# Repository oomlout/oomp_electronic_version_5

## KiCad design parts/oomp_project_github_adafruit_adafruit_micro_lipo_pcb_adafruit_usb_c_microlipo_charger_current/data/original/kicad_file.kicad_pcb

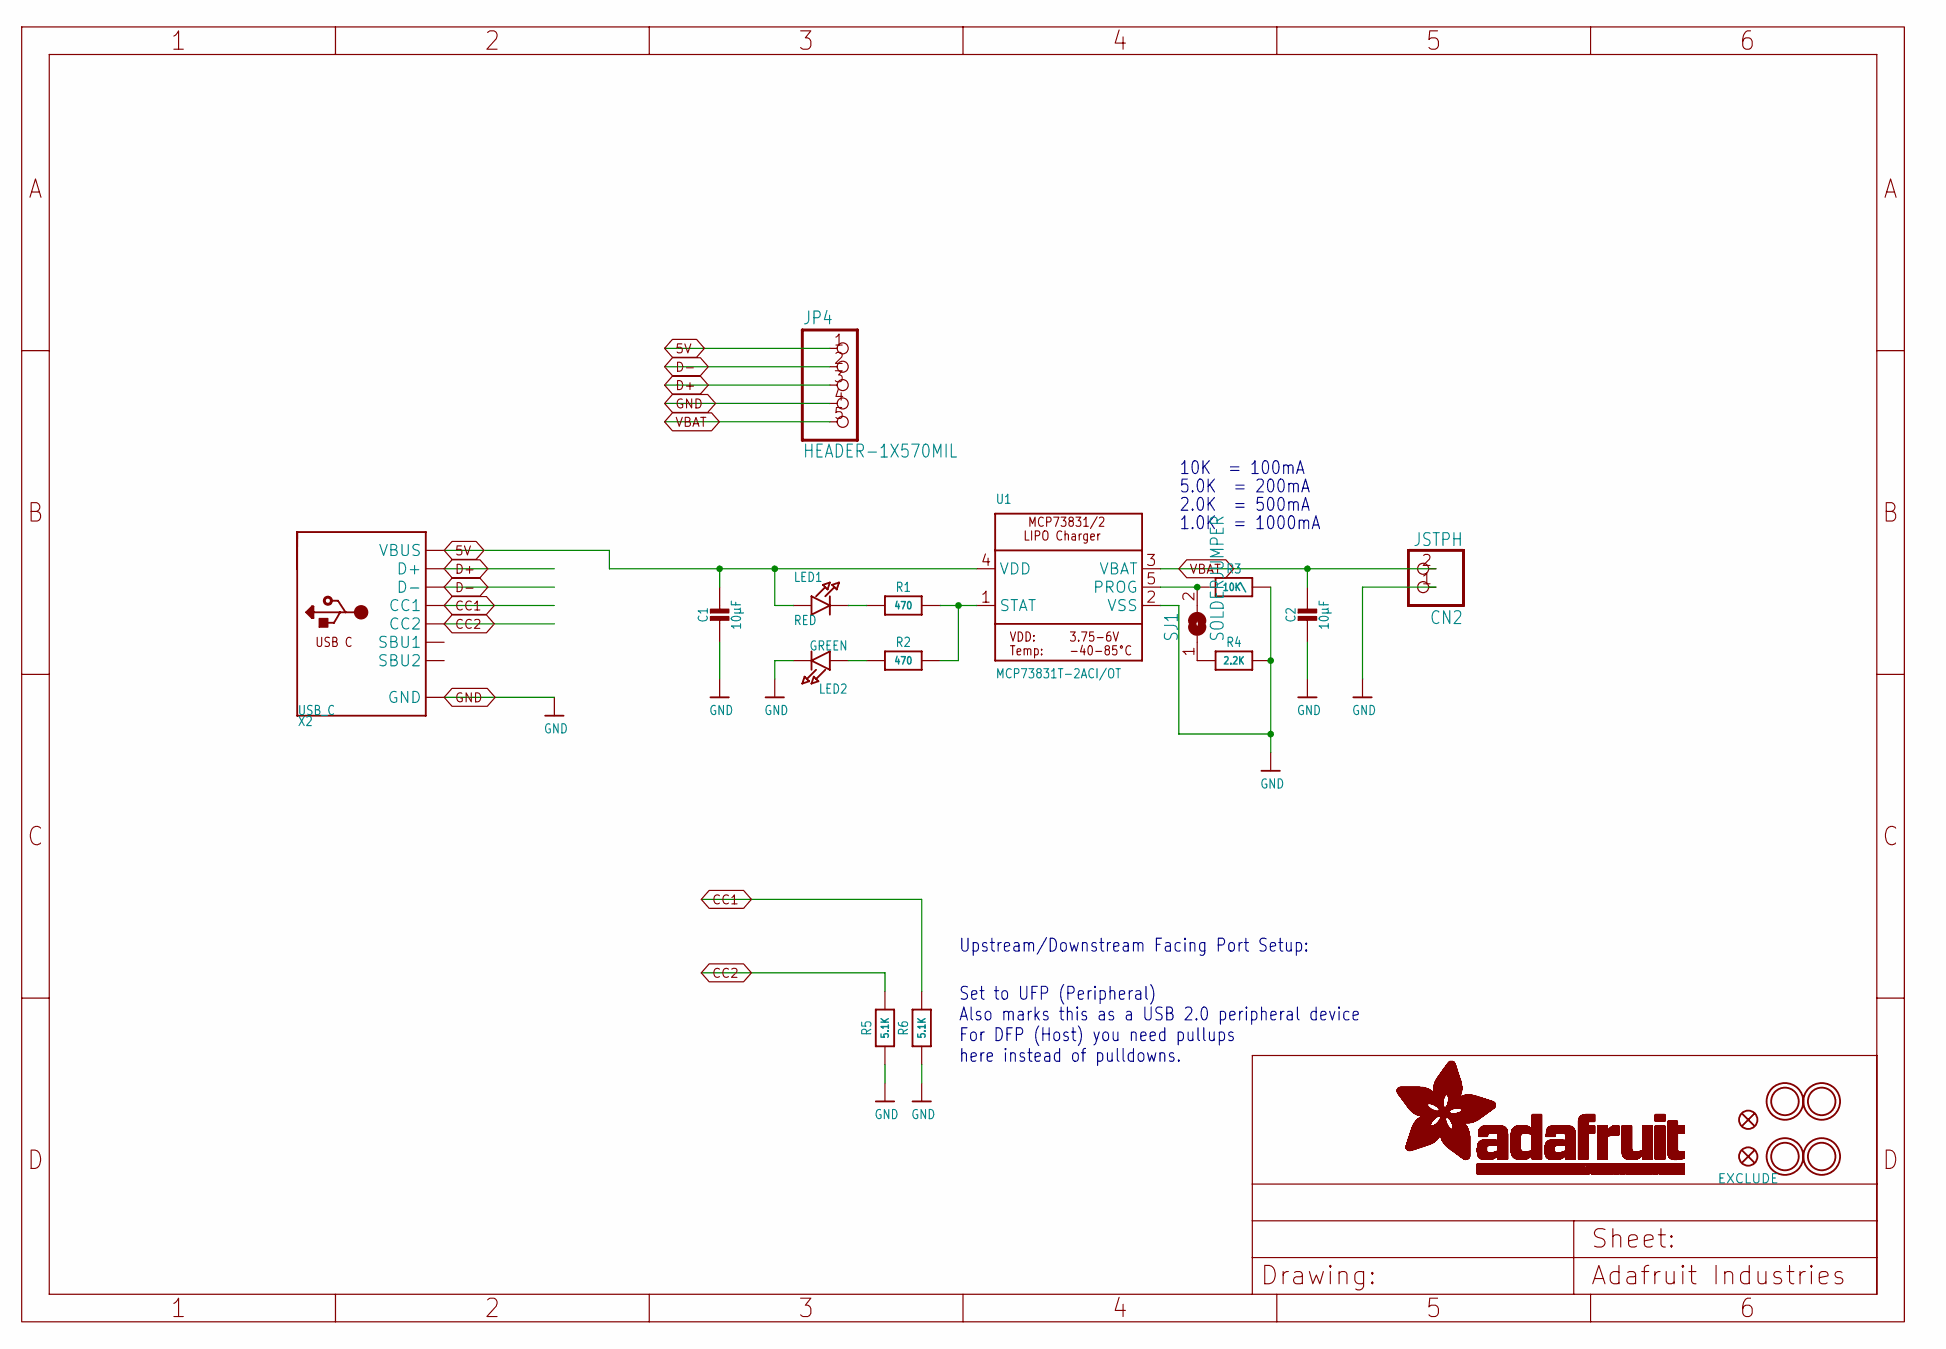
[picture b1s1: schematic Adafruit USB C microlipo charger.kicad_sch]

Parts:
C1, C2: 10µF; 0805-NO@1
CN2: JSTPH; JSTPH2
FID1, FID2: FIDUCIAL""; FIDUCIAL_1MM
JP4: HEADER-1X570MIL; 1X05_ROUND_70
LED1: RED; CHIPLED_0805_NOOUTLINE
LED2: GREEN; CHIPLED_0805_NOOUTLINE
R1, R2: 470; 0603-NO
R3: 10K\; 0603-NO
R4: 2.2K; 0603-NO
R5, R6: 5.1K; 0603-NO
SJ1: SOLDERJUMPER; SOLDERJUMPER_ARROW_NOPASTE
U1: MCP73831T-2ACI/OT; SOT23-5
U$9, U$10, U$11, U$12: MOUNTINGHOLE2.5; MOUNTINGHOLE_2.5_PLATED
X2: USB_C; USB_C_CUSB31-CFM2AX-01-X

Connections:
5V: C1.1, JP4.1, LED1.A, U1.4 (VDD), X2.A4B9 (VBUS), X2.B4A9 (VBUS)
CC1: R6.2, X2.A5 (CC1)
CC2: R5.2, X2.B5 (CC2)
D+: JP4.3, X2.A6 (D+), X2.B6 (D+)
D-: JP4.2, X2.A7 (D-), X2.B7 (D-)
GND: C1.2, C2.2, CN2.1, JP4.4, LED2.C, R3.2, R4.2, R5.1, R6.1, U1.2 (VSS), X2.A1B12 (GND), X2.B1A12 (GND)
unnamed: LED1.C, R1.1
unnamed: R1.2, R2.2, U1.1 (STAT)
unnamed: R4.1, SJ1.1
unnamed: R3.1, SJ1.2, U1.5 (PROG)
unnamed: LED2.A, R2.1
VBAT: C2.1, CN2.2, JP4.5, U1.3 (VBAT)

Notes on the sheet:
10K = 100mA
Upstream/Downstream Facing Port Setup:
Set to UFP (Peripheral) Also marks this as a USB 2.0 peripheral device For DFP (Host) you need pullups here instead of pulldowns.
1.0K = 1000mA
2.0K = 500mA
5.0K = 200mA

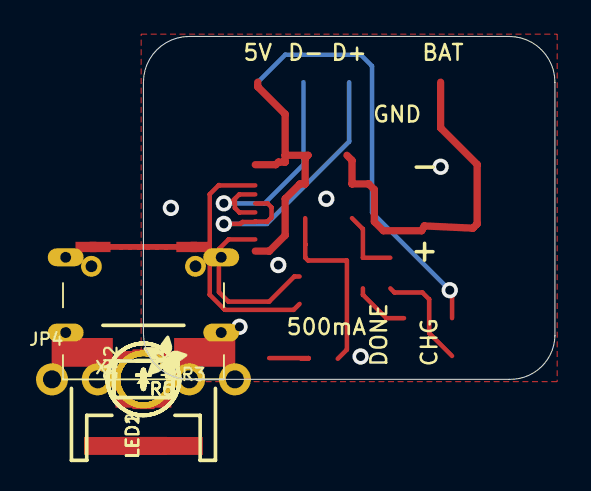
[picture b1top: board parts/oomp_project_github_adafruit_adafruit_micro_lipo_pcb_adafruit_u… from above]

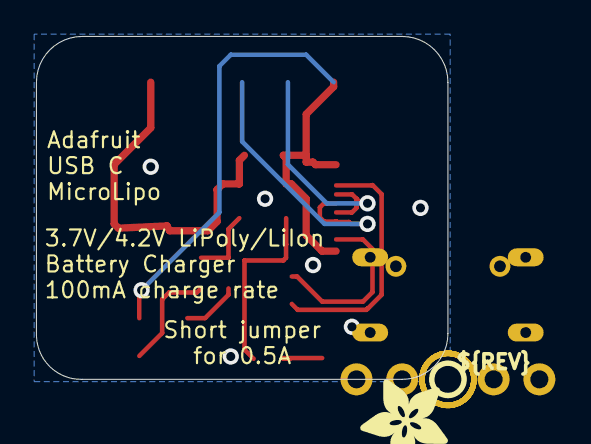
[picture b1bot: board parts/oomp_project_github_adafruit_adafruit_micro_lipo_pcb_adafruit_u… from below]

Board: 2 copper layers, 22.9 x 19.1 mm, 24 parts (2 on the bottom side), 12 nets.

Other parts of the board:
U$2: ADAFRUIT_2.5MM
U$13: ADAFRUIT_5MM
U$16: PCBFEAT-REV-040

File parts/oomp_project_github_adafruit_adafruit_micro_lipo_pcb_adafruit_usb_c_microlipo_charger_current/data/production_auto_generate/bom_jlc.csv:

Comment,Designator,Footprint,LCSC Part #
,JP4,Adafruit USB C microlipo charger-import-fps:1X05_ROUND_70,C42431835
,U$2,Adafruit USB C microlipo charger-import-fps:ADAFRUIT_2.5MM,
,U$13,Adafruit USB C microlipo charger-import-fps:ADAFRUIT_5MM,
,U$16,Adafruit USB C microlipo charger-import-fps:PCBFEAT-REV-040,
,X2,Adafruit USB C microlipo charger-import-fps:USB_C_CUSB31-CFM2AX-01-X,
10K\,R3,Adafruit USB C microlipo charger-import-fps:0603-NO,C98220
10µF,"C1,C2",Adafruit USB C microlipo charger-import-fps:0805-NO@1,
2.2K,R4,Adafruit USB C microlipo charger-import-fps:0603-NO,C4190
470,"R1,R2",Adafruit USB C microlipo charger-import-fps:0603-NO,C23179
5.1K,"R5,R6",Adafruit USB C microlipo charger-import-fps:0603-NO,C23186
GREEN,LED2,Adafruit USB C microlipo charger-import-fps:CHIPLED_0805_NOOUTLINE,
JSTPH,CN2,Adafruit USB C microlipo charger-import-fps:JSTPH2,
MCP73831T-2ACI/OT,U1,Adafruit USB C microlipo charger-import-fps:SOT23-5,
RED,LED1,Adafruit USB C microlipo charger-import-fps:CHIPLED_0805_NOOUTLINE,

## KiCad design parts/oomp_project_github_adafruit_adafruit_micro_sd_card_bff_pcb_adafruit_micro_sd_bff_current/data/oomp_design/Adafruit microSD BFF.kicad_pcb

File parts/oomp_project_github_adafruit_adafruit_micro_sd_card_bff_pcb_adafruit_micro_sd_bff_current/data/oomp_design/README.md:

# OOMP KiCad design copy

Open `Adafruit microSD BFF.kicad_pro` (or the `.kicad_pcb` / `.kicad_sch`) in KiCad. Local OOMP libraries are under `libraries/`. Original inputs are preserved in [../original/](../original/).

Only verified unchanged installed KiCad defaults were renamed. Modified, custom, unmatched and unavailable items remain unchanged. Soldering variants are never swapped during conversion. Existing pad coordinates, nets and UUIDs are preserved.

See [conversion_report.yaml](conversion_report.yaml) for every conversion and skip. Copy this directory before editing; regeneration refuses to overwrite edited design files.

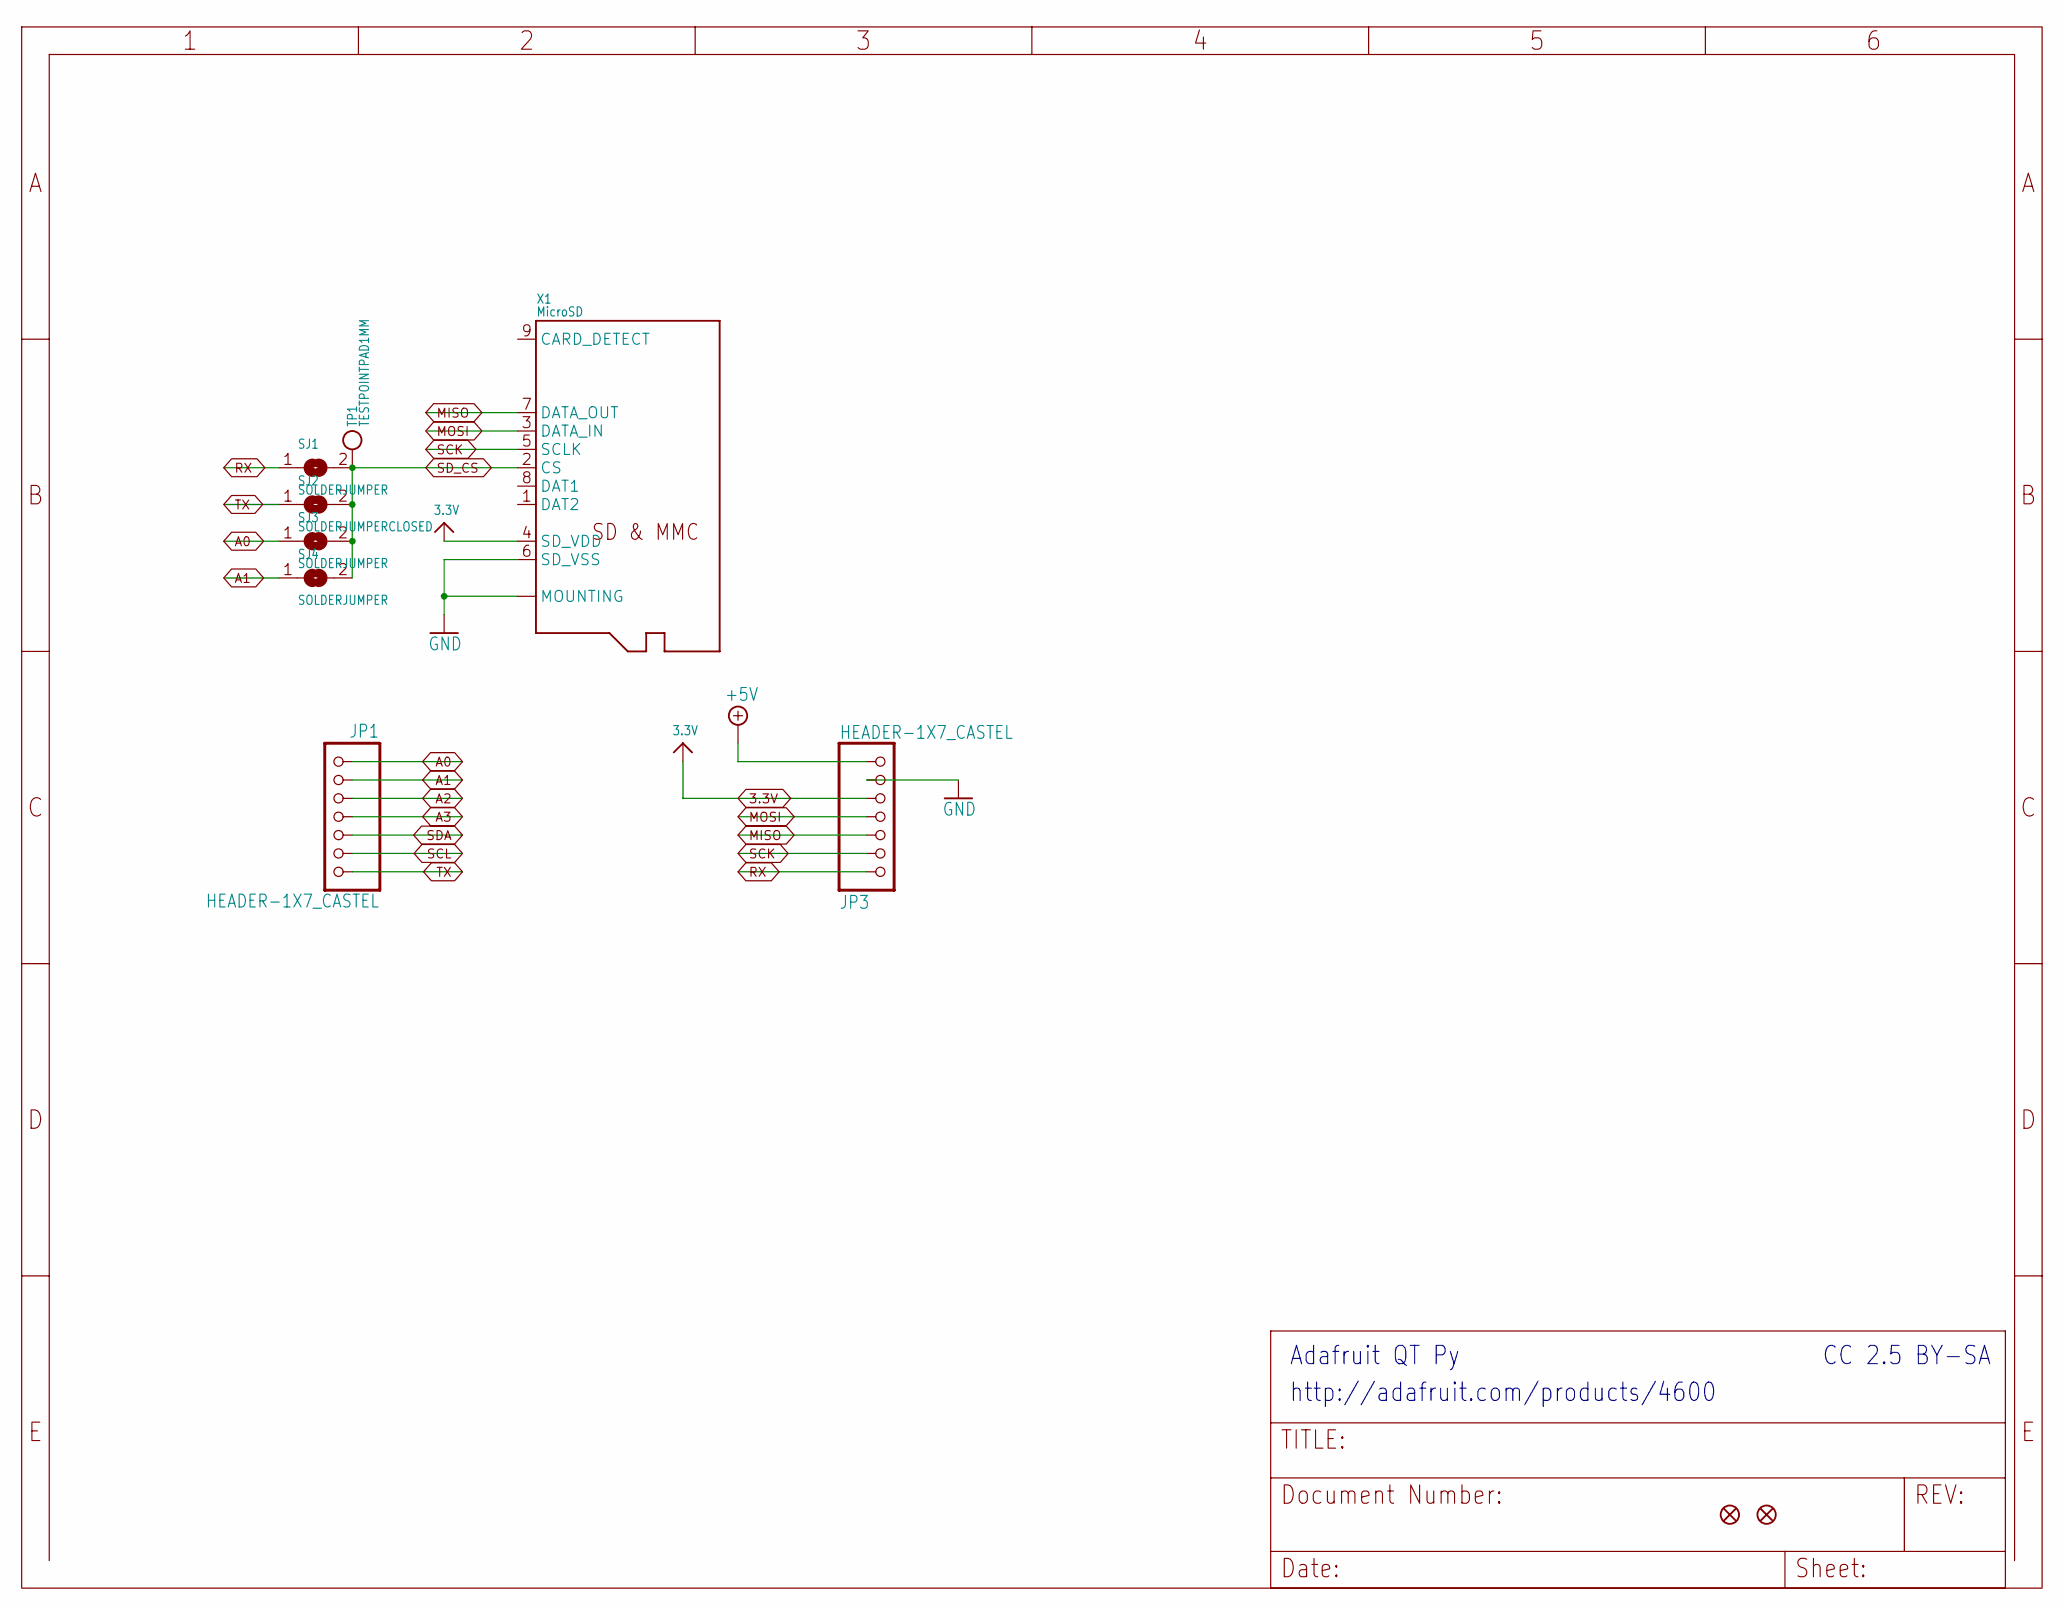
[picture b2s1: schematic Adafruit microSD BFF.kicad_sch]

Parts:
JP1, JP3: HEADER-1X7_CASTEL; 1X07_CASTEL
SJ1, SJ3, SJ4: SOLDERJUMPER; SOLDERJUMPER_ARROW_NOPASTE
SJ2: SOLDERJUMPERCLOSED; SOLDERJUMPER_CLOSEDWIRE
TP1: TESTPOINTPAD1MM; TESTPOINT_PAD_1MM
U$6, U$8: FIDUCIAL_1MM
X1: MicroSD; MOLEX_104031-0811

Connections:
3.3V: JP3.5, JP3.5C (5), X1.4 (SD_VDD)
+5V: JP3.7, JP3.7C (7)
A0: JP1.1, JP1.1C (1), SJ3.1
A1: JP1.2, JP1.2C (2), SJ4.1
A2: JP1.3, JP1.3C (3)
A3: JP1.4, JP1.4C (4)
GND: JP3.6, JP3.6C (6), X1.6 (SD_VSS), X1.10 (MOUNTING), X1.G1 (MOUNTING), X1.G2 (MOUNTING), X1.G3 (MOUNTING), X1.G4 (MOUNTING)
MISO: JP3.3, JP3.3C (3), X1.7 (DATA_OUT)
MOSI: JP3.4, JP3.4C (4), X1.3 (DATA_IN)
RX: JP3.1, JP3.1C (1), SJ1.1
SCK: JP3.2, JP3.2C (2), X1.5 (SCLK)
SCL: JP1.6, JP1.6C (6)
SDA: JP1.5, JP1.5C (5)
SD_CS: SJ1.2, SJ2.2, SJ3.2, SJ4.2, TP1.P$1, X1.2 (CS)
TX: JP1.7, JP1.7C (7), SJ2.1

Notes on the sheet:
CC 2.5 BY-SA
Adafruit QT Py
http://adafruit.com/products/4600

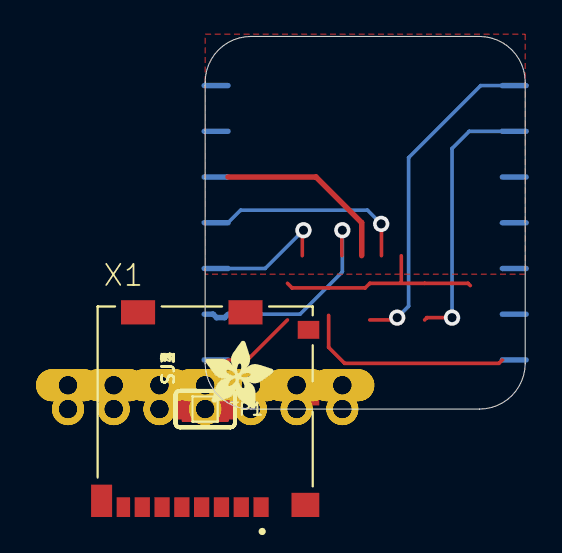
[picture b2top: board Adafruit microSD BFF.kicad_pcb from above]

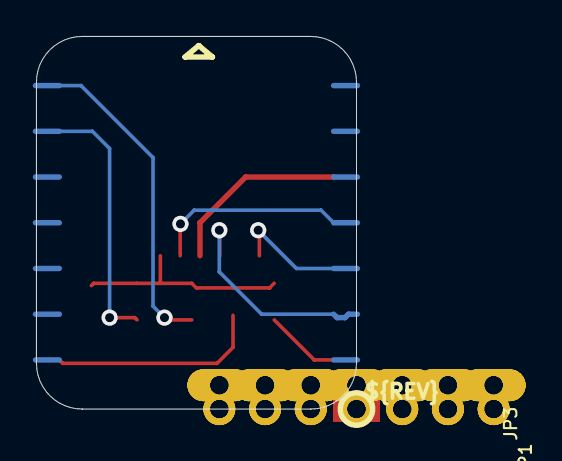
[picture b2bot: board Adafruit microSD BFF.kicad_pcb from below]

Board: 16 copper layers, 17.8 x 20.7 mm, 20 parts (5 on the bottom side), 15 nets.

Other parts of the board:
PLABEL0: PLABEL0
PLABEL1: PLABEL1
PLABEL2: PLABEL2
PLABEL3: PLABEL3
PLABEL4: PLABEL4
PLABEL5: PLABEL5
PLABEL6: PLABEL6
PLABEL7: PLABEL7
U$2: ADAFRUIT_3.5MM
U$3: PCBFEAT-REV-040

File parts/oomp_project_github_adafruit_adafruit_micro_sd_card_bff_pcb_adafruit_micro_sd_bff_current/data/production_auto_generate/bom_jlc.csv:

Comment,Designator,Footprint,LCSC Part #
,"JP1,JP3",Adafruit microSD BFF-import-fps:1X07_CASTEL,C7501585
,U$2,Adafruit microSD BFF-import-fps:ADAFRUIT_3.5MM,
,U$3,Adafruit microSD BFF-import-fps:PCBFEAT-REV-040,
,PLABEL0,Adafruit microSD BFF-import-fps:PLABEL0,
,PLABEL1,Adafruit microSD BFF-import-fps:PLABEL1,
,PLABEL2,Adafruit microSD BFF-import-fps:PLABEL2,
,PLABEL3,Adafruit microSD BFF-import-fps:PLABEL3,
,PLABEL4,Adafruit microSD BFF-import-fps:PLABEL4,
,PLABEL5,Adafruit microSD BFF-import-fps:PLABEL5,
,PLABEL6,Adafruit microSD BFF-import-fps:PLABEL6,
,PLABEL7,Adafruit microSD BFF-import-fps:PLABEL7,
,TP1,Adafruit microSD BFF-import-fps:TESTPOINT_PAD_1MM,
FIDUCIAL_1MM,"U$6,U$8",Adafruit microSD BFF-import-fps:FIDUCIAL_1MM,
MicroSD,X1,Adafruit microSD BFF-import-fps:MOLEX_104031-0811,

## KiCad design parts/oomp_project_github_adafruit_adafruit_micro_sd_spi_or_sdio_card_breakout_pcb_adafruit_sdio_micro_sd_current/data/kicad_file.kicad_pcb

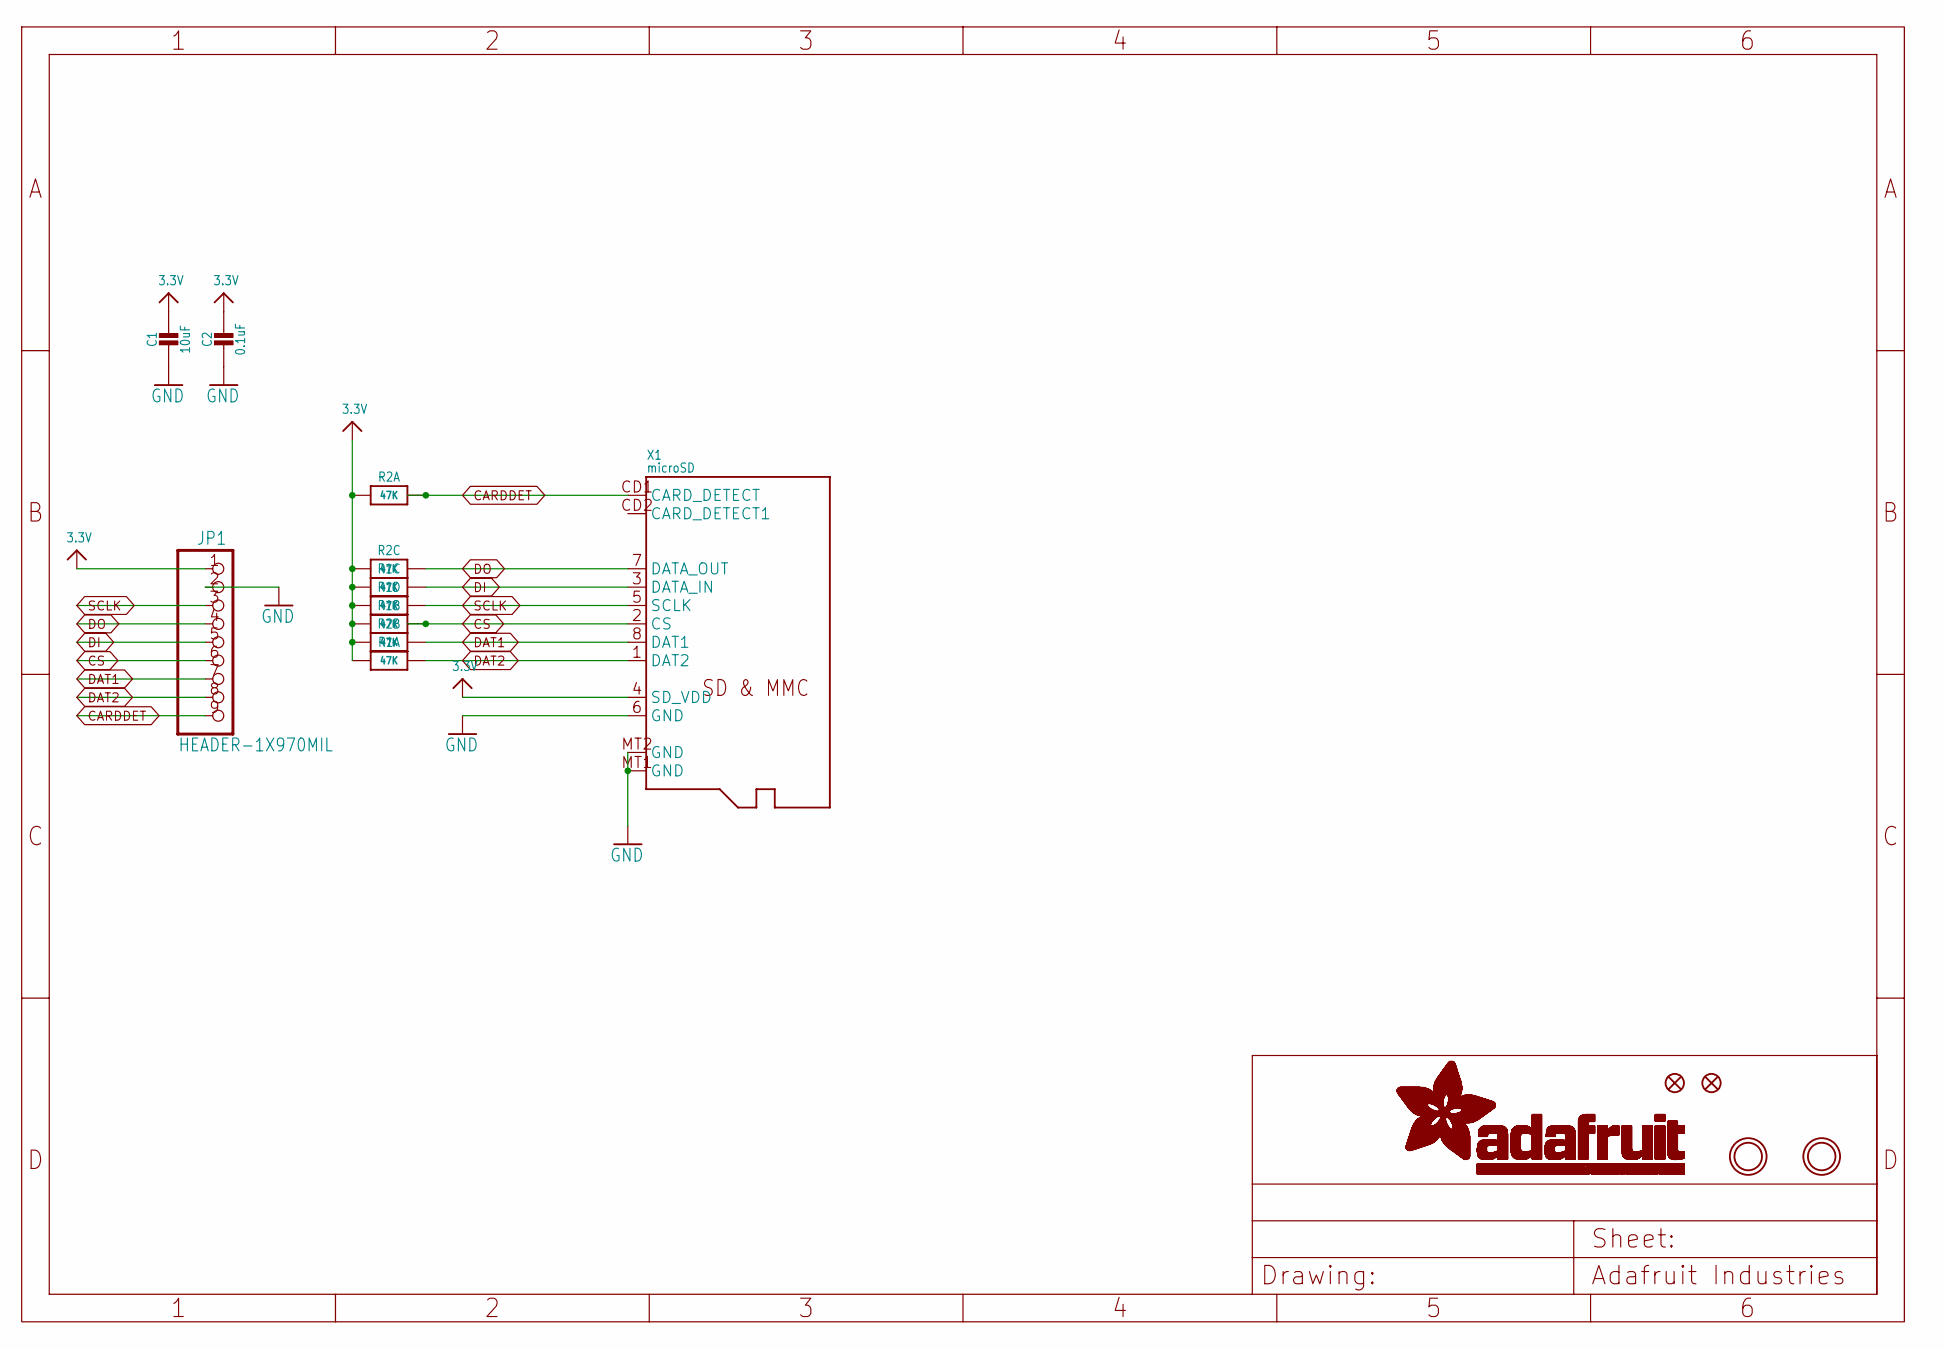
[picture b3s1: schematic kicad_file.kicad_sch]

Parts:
C1: 10uF; 0805-NO
C2: 0.1uF; 0603-NO
FID1, FID2: FIDUCIAL""; FIDUCIAL_1MM
JP1: HEADER-1X970MIL; 1X09_ROUND_70
R1, R2: 47K; RESPACK_4X0603
U$1, U$2: MOUNTINGHOLE2.5; MOUNTINGHOLE_2.5_PLATED
X1: microSD; MICROSD

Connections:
3.3V: C1.1, C2.1, JP1.1, R1.1, R1.2 (1), R1.3 (1), R1.4 (1), R2.1, R2.2 (1), R2.3 (1), X1.4 (SD_VDD)
CARDDET: JP1.9, R2.8 (2), X1.CD1 (CARD_DETECT)
CS: JP1.6, R1.7 (2), X1.2 (CS)
DAT1: JP1.7, R2.7 (2), X1.8 (DAT1)
DAT2: JP1.8, R1.8 (2), X1.1 (DAT2)
DI: JP1.5, R1.6 (2), X1.3 (DATA_IN)
DO: JP1.4, R2.6 (2), X1.7 (DATA_OUT)
GND: C1.2, C2.2, JP1.2, X1.6 (GND), X1.MT1 (GND), X1.MT2 (GND)
SCLK: JP1.3, R1.5 (2), X1.5 (SCLK)

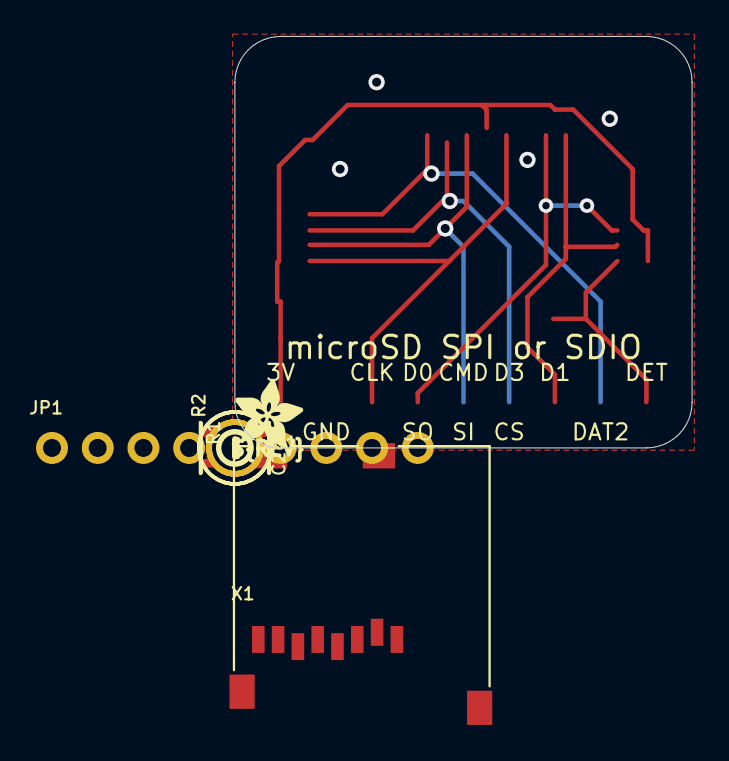
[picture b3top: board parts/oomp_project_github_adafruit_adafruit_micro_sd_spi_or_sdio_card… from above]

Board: 2 copper layers, 25.4 x 22.9 mm, 12 parts (0 on the bottom side), 9 nets.

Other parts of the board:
U$4: ADAFRUIT_3.5MM
U$7: PCBFEAT-REV-040

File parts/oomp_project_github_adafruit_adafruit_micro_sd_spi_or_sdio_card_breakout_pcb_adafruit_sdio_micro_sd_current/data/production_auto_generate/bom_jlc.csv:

Comment,Designator,Footprint,LCSC Part #
,JP1,Adafruit SDIO microSD-import-fps:1X09_ROUND_70,C2932701
,U$4,Adafruit SDIO microSD-import-fps:ADAFRUIT_3.5MM,
,U$7,Adafruit SDIO microSD-import-fps:PCBFEAT-REV-040,
0.1uF,C2,Adafruit SDIO microSD-import-fps:0603-NO,C14663
10uF,C1,Adafruit SDIO microSD-import-fps:0805-NO,
47K,"R1,R2",Adafruit SDIO microSD-import-fps:RESPACK_4X0603,C2907042
microSD,X1,Adafruit SDIO microSD-import-fps:MICROSD,

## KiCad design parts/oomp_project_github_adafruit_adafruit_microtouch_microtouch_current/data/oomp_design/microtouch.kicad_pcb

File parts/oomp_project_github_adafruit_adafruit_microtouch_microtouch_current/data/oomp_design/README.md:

# OOMP KiCad design copy

Open `microtouch.kicad_pro` (or the `.kicad_pcb` / `.kicad_sch`) in KiCad. Local OOMP libraries are under `libraries/`. Original inputs are preserved in [../original/](../original/).

Only verified unchanged installed KiCad defaults were renamed. Modified, custom, unmatched and unavailable items remain unchanged. Soldering variants are never swapped during conversion. Existing pad coordinates, nets and UUIDs are preserved.

See [conversion_report.yaml](conversion_report.yaml) for every conversion and skip. Copy this directory before editing; regeneration refuses to overwrite edited design files.

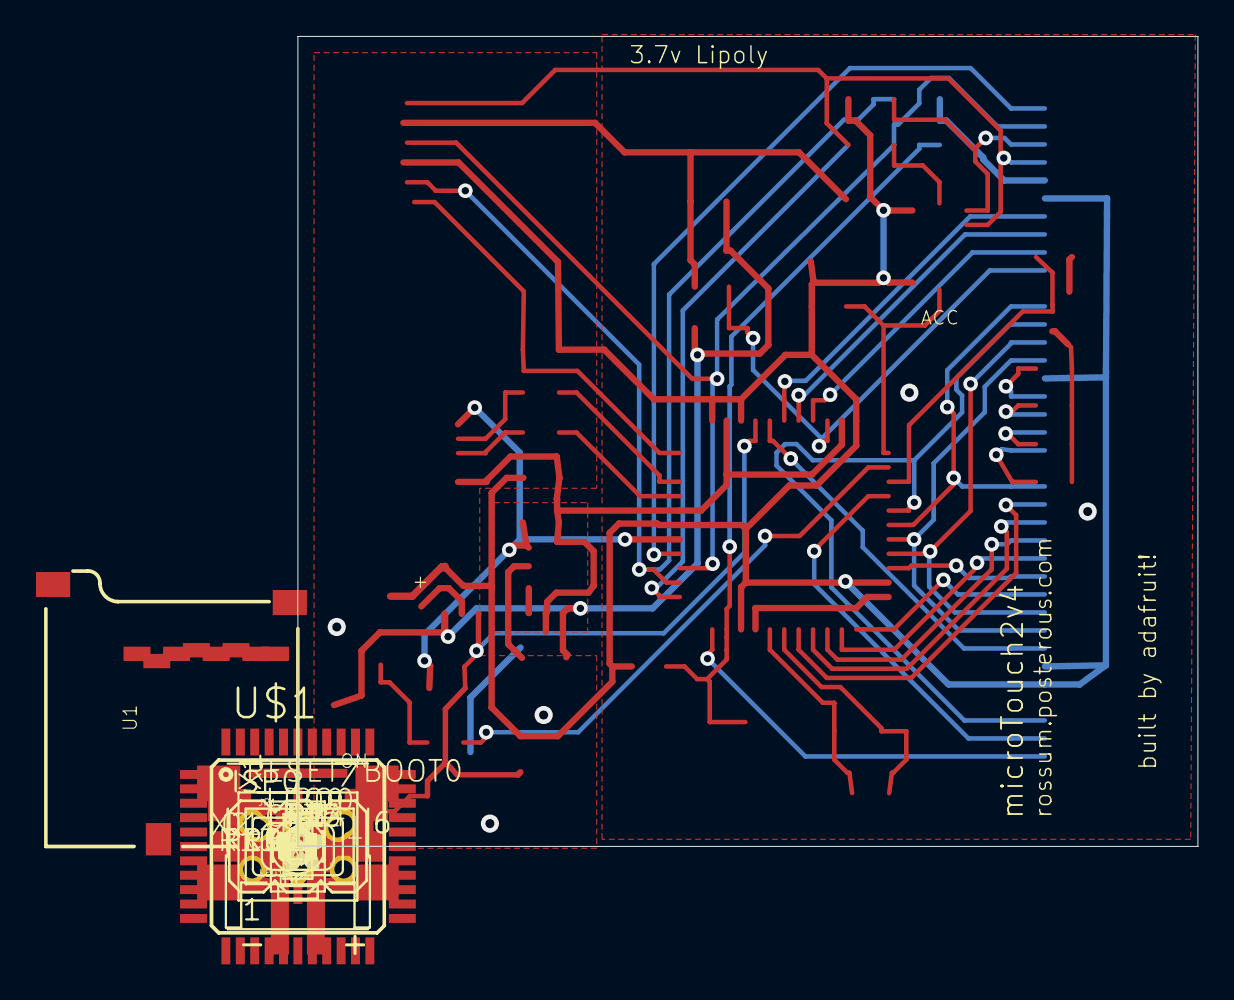
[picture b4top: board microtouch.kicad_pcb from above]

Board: 16 copper layers, 50.0 x 45.0 mm, 42 parts (1 on the bottom side), 45 nets.

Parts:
ACCELEROMERTER0: MMA7455; LGA
C1, C2: 18pf; C0805K
C3, C5, C6, C8: 1uf; C0805K
C4: 10uF; A_3216-18R
ISP0: ISP; MA03-2
JP1: BATT; JSTPH2
LDO0: LP298XS; SOT23-5L
LED1: RED; CHIPLED_0805
LIPO0: MCP73811/2; SOT23-5L
Q1: PN2222; SOT23-BEC
R1, R2, R8, R9, R10, R11: 22; R0805
R3, R15: 10k; M0805
R4, R14, R16: 10k; R0805
R5, R7: 1k; R0805
R6: 100k; R0805
R12, R13: 100K; M0805
R17: 4.7K; M0805
RESET/BOOT0: EVQQ2; EVQ-Q2
U1: MICROSD; MICRO-SD-SOCKET-PP
U2: KSSMINISWITCH; KSSMINI
U$1: ATMEGA32U4; TQFP44
U$2: LCD37; LCD371MM
U$6, U$7, U$8: FIDUCIAL; FIDUCIAL_1MM
U$9: ADAFRUIT200MIL
X1: USBSMD; USB-MINIB
X2: 16Mhz; NX5032

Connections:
5V: C6.1, LIPO0.1, LIPO0.4, R14.1, U$1.7, X1.VBUS
ACCCS: ACCELEROMERTER0.7, R3.2, U$1.33
BLED: R7.1, U$1.31
CS: U$1.39, U$2.7
DB0: U$1.8, U$2.1
DB4: U$1.28, U$2.12, U$2.22
DB5: U$1.29, U$2.13, U$2.35
DB6: U$1.30, U$2.36
DB7: U$1.12, U$2.37
DB8: U$1.18, U$2.23
DB9: U$1.19, U$2.24
DB10: U$1.20, U$2.25
DB11: U$1.21, U$2.26
DB12: U$1.25, U$2.27
DB13: U$1.22, U$2.28
DB14: U$1.26, U$2.14, U$2.29
DB15: U$1.27, U$2.15, U$2.30
GND: ACCELEROMERTER0.2, ACCELEROMERTER0.3, ACCELEROMERTER0.4, ACCELEROMERTER0.5, ACCELEROMERTER0.10, ACCELEROMERTER0.11, C1.2, C2.2, C3.2, C4.-, C5.2, C6.2, C8.2, ISP0.6, JP1.1, LDO0.2, LED1.C, LIPO0.2, Q1.E, R6.2, R13.2, R17.2, RESET/BOOT0.A', U1.6, U$1.5, U$1.15, U$1.23, U$1.35, U$1.43, U$2.5, U$2.11, U$2.21, U$2.34, X1.GND
LED: R5.2, U$1.32
LIPO: C8.1, JP1.2, LDO0.1, LIPO0.3, R12.1, U2.P$1
LRESET: U$1.40, U$2.31
MISO: ACCELEROMERTER0.12, ISP0.1, U1.7, U$1.11, U$2.4
MMCCS: R4.2, U1.2, U$1.1
MOSI: ACCELEROMERTER0.13, ISP0.4, U1.3, U$1.10, U$2.3
unnamed: LIPO0.5, R17.1
unnamed: R1.1, X1.D+
unnamed: R2.1, X1.D-
unnamed: R10.2, U$2.19
unnamed: R8.2, U$2.17
unnamed: R9.2, U$2.18
unnamed: R11.2, U$2.20
unnamed: Q1.C, R8.1, R9.1, R10.1, R11.1
unnamed: Q1.B, R7.2
unnamed: LED1.A, R5.1
unnamed: R1.2, U$1.4
unnamed: R2.2, U$1.3
RD: R12.2, R13.1, U$1.36, U$2.10
REGEN: LDO0.3, R6.1, R14.2, R16.2, U2.P$2, U$1.41
RESET: ISP0.5, R15.2, RESET/BOOT0.B', U$1.13
RS: U$1.38, U$2.8
SCLK: ACCELEROMERTER0.14, ISP0.3, U1.5, U$1.9, U$2.2
VCC: ACCELEROMERTER0.1, ACCELEROMERTER0.6, C3.1, C4.+, C5.1, ISP0.2, LDO0.5, R3.1, R4.1, R15.1, R16.1, U1.4, U$1.6, U$1.14, U$1.24, U$1.34, U$1.42, U$1.44, U$2.6, U$2.16, U$2.32, U$2.33
WR: U$1.37, U$2.9
XTAL1: C1.1, U$1.16, X2.P$1
XTAL2: C2.1, U$1.17, X2.P$2

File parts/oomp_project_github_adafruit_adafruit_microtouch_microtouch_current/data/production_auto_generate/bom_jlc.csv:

Comment,Designator,Footprint,LCSC Part #
,U$9,microtouch-import-fps:ADAFRUIT200MIL,
100K,"R12,R13",microtouch-import-fps:M0805,C149504
100k,R6,microtouch-import-fps:R0805,C149504
10k,"R3,R15",microtouch-import-fps:M0805,C17414
10k,"R4,R14,R16",microtouch-import-fps:R0805,C17414
10uF,C4,microtouch-import-fps:A_3216-18R,
16Mhz,X2,microtouch-import-fps:NX5032,
18pf,"C1,C2",microtouch-import-fps:C0805K,
1k,"R5,R7",microtouch-import-fps:R0805,C17513
1uf,"C3,C5,C6,C8",microtouch-import-fps:C0805K,
22,"R1,R2,R8,R9,R10,R11",microtouch-import-fps:R0805,C2907310
4.7K,R17,microtouch-import-fps:M0805,C2907264
ATMEGA32U4,U$1,microtouch-import-fps:TQFP44,
BATT,JP1,microtouch-import-fps:JSTPH2,
EVQQ2,RESET/BOOT0,microtouch-import-fps:EVQ-Q2,
FIDUCIAL,"U$6,U$7,U$8",microtouch-import-fps:FIDUCIAL_1MM,
ISP,ISP0,microtouch-import-fps:MA03-2,
KSSMINISWITCH,U2,microtouch-import-fps:KSSMINI,
LCD37,U$2,microtouch-import-fps:LCD371MM,
LP298XS,LDO0,microtouch-import-fps:SOT23-5L,
MCP73811/2,LIPO0,microtouch-import-fps:SOT23-5L,
MICROSD,U1,microtouch-import-fps:MICRO-SD-SOCKET-PP,
MMA7455,ACCELEROMERTER0,microtouch-import-fps:LGA,
PN2222,Q1,microtouch-import-fps:SOT23-BEC,
RED,LED1,microtouch-import-fps:CHIPLED_0805,
USBSMD,X1,microtouch-import-fps:USB-MINIB,

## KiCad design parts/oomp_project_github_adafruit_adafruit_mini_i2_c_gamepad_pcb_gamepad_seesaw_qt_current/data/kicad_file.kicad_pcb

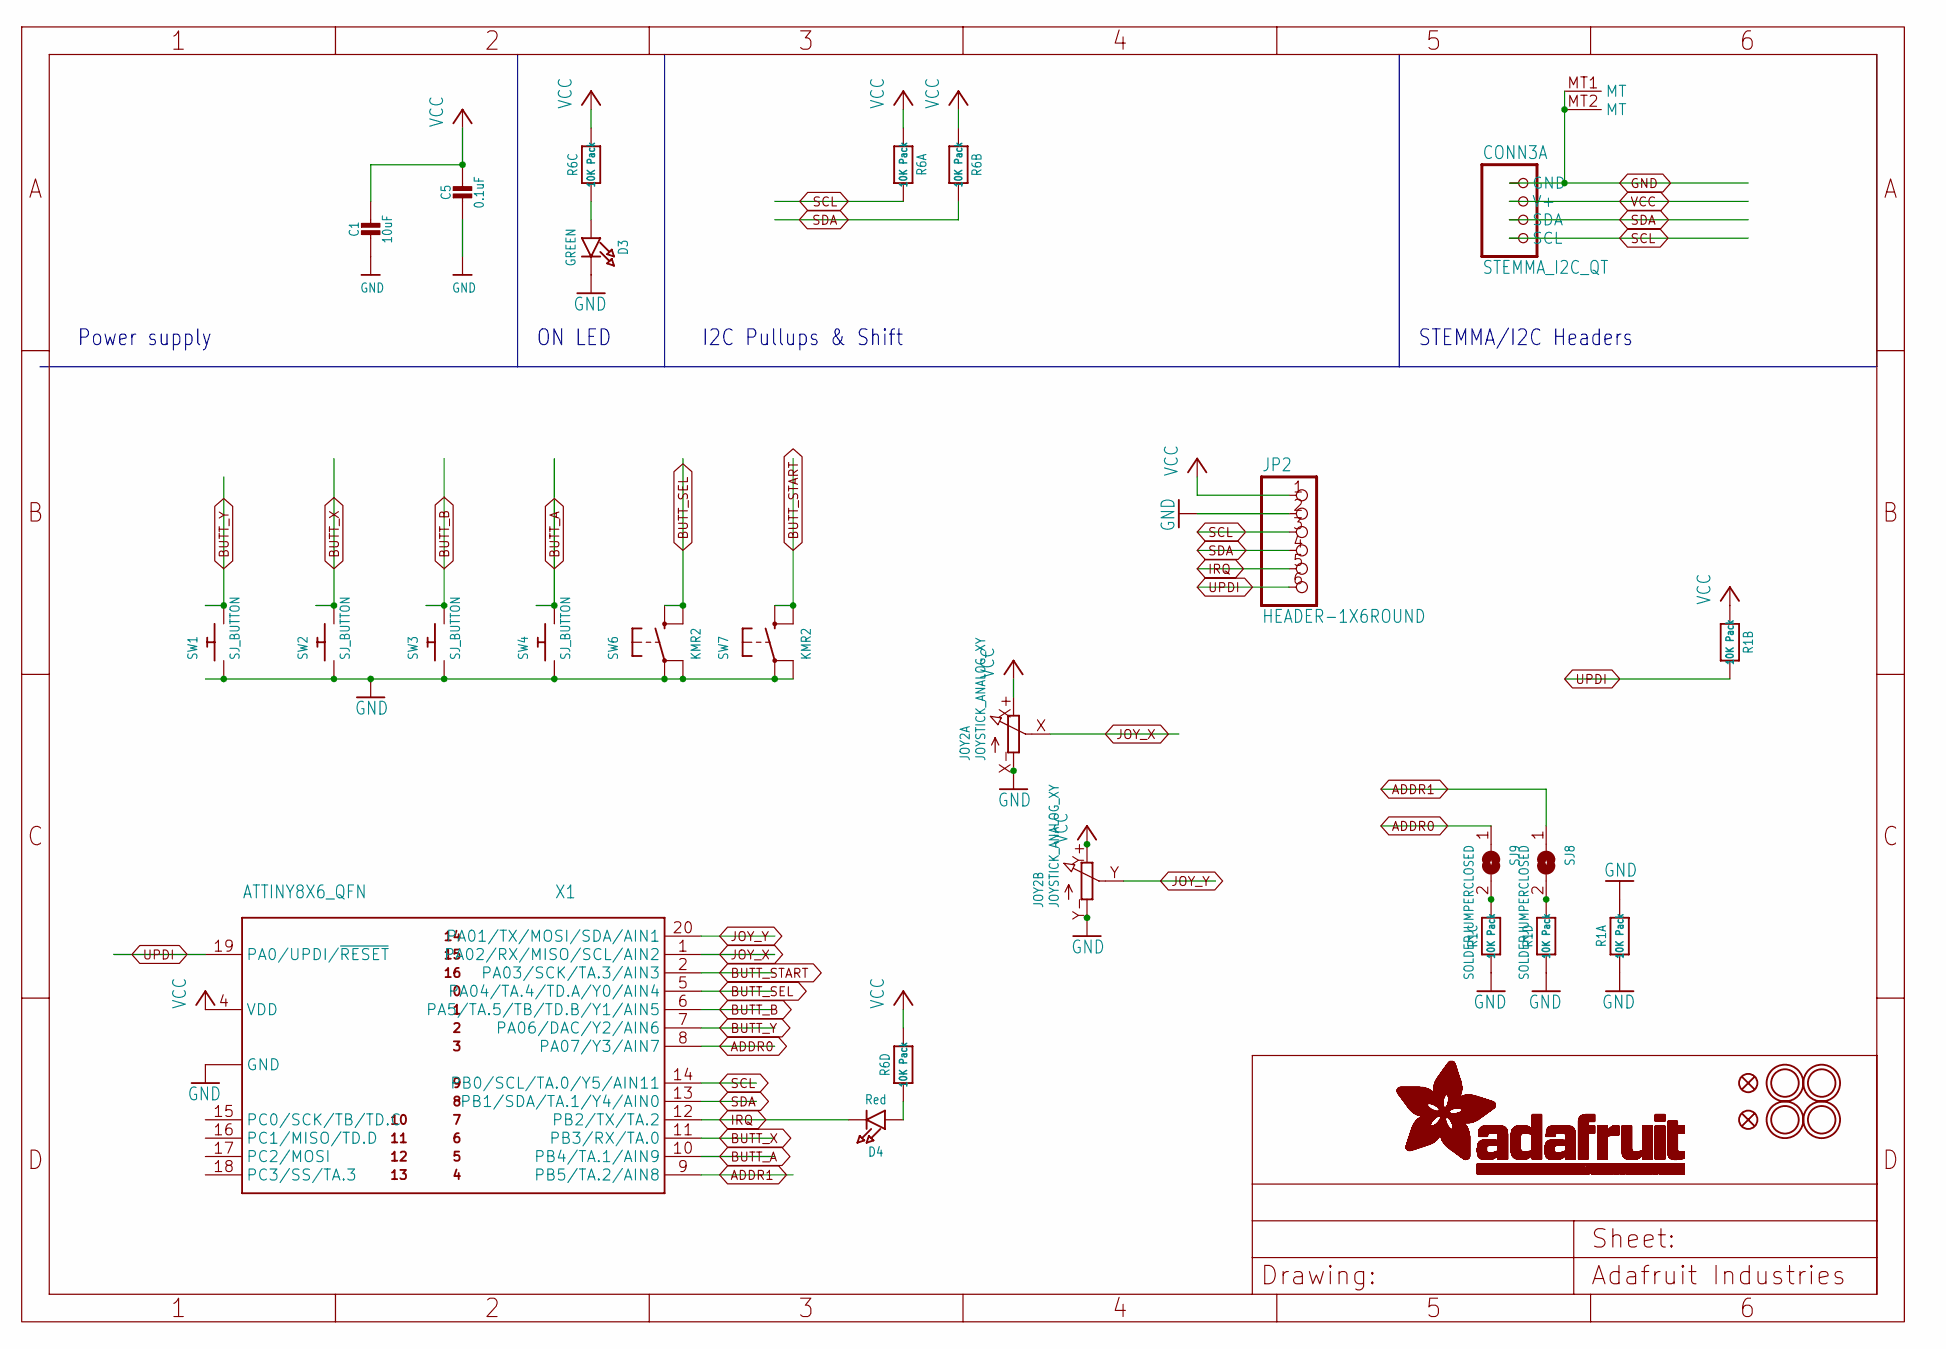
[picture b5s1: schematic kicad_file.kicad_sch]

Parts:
C1: 10uF; 0805-NO
C5: 0.1uF; 0603-NO
CONN3: STEMMA_I2C_QT; JST_SH4; LCSC C2845363
D3: GREEN; CHIPLED_0603_NOOUTLINE
D4: Red; CHIPLED_0603_NOOUTLINE
FID1, FID2: FIDUCIAL_1MM
JOY2: JOYSTICK_ANALOG_XY; JOYSTICK_ANALOG_MINITHM
JP2: HEADER-1X6ROUND; 1X06_ROUND
R1, R6: 10K Pack; RESPACK_4X0603
SJ8, SJ9: SOLDERJUMPERCLOSED; SOLDERJUMPER_CLOSEDWIRE
SW1, SW2, SW3, SW4: SJ_BUTTON; PUSHBUTTON_SMD_SJ
SW6, SW7: KMR2; BTN_RKB2_4.6X2.8
U$1, U$2, U$3, U$4: MOUNTINGHOLE2.5; MOUNTINGHOLE_2.5_PLATED
X1: ATTINY8X6_QFN; QFN20_3MM

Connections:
ADDR0: SJ9.1, X1.8 (PA07/Y3/AIN7)
ADDR1: SJ8.1, X1.9 (PB5/TA.2/AIN8)
BUTT_A: SW4.P$2, X1.10 (PB4/TA.1/AIN9)
BUTT_B: SW3.P$2, X1.6 (PA5/TA.5/TB/TD.B/Y1/AIN5)
BUTT_SEL: SW6.B (S), SW6.B' (S1), X1.5 (PA04/TA.4/TD.A/Y0/AIN4)
BUTT_START: SW7.B (S), SW7.B' (S1), X1.2 (PA03/SCK/TA.3/AIN3)
BUTT_X: SW2.P$2, X1.11 (PB3/RX/TA.0)
BUTT_Y: SW1.P$2, X1.7 (PA06/DAC/Y2/AIN6)
GND: C1.2, C5.2, CONN3.1 (GND), CONN3.MT1 (MT), CONN3.MT2 (MT), D3.C, JOY2.X- (A), JOY2.Y- (A), JP2.2, R1.1, R1.3 (1), R1.4 (1), R1.8 (2), SW1.P$1, SW2.P$1, SW3.P$1, SW4.P$1, SW6.A, SW6.A' (P1), SW7.A, SW7.A' (P1), X1.3 (GND), X1.PAD (GND)
IRQ: D4.C, JP2.5, X1.12 (PB2/TX/TA.2)
JOY_X: JOY2.X (S), X1.1 (PA02/RX/MISO/SCL/AIN2)
JOY_Y: JOY2.Y (S), X1.20 (PA01/TX/MOSI/SDA/AIN1)
unnamed: D3.A, R6.3 (1)
unnamed: R1.6 (2), SJ9.2
unnamed: R1.5 (2), SJ8.2
unnamed: D4.A, R6.4 (1)
SCL: CONN3.4 (SCL), JP2.3, R6.8 (2), X1.14 (PB0/SCL/TA.0/Y5/AIN11)
SDA: CONN3.3 (SDA), JP2.4, R6.7 (2), X1.13 (PB1/SDA/TA.1/Y4/AIN0)
UPDI: JP2.6, R1.7 (2), X1.19 (PA0/UPDI/~RESET)
VCC: C1.1, C5.1, CONN3.2 (V+), JOY2.X+ (E), JOY2.Y+ (E), JP2.1, R1.2 (1), R6.1, R6.2 (1), R6.5 (2), R6.6 (2), X1.4 (VDD)

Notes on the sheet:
I2C Pullups & Shift
STEMMA/I2C Headers
Power supply
ON LED
